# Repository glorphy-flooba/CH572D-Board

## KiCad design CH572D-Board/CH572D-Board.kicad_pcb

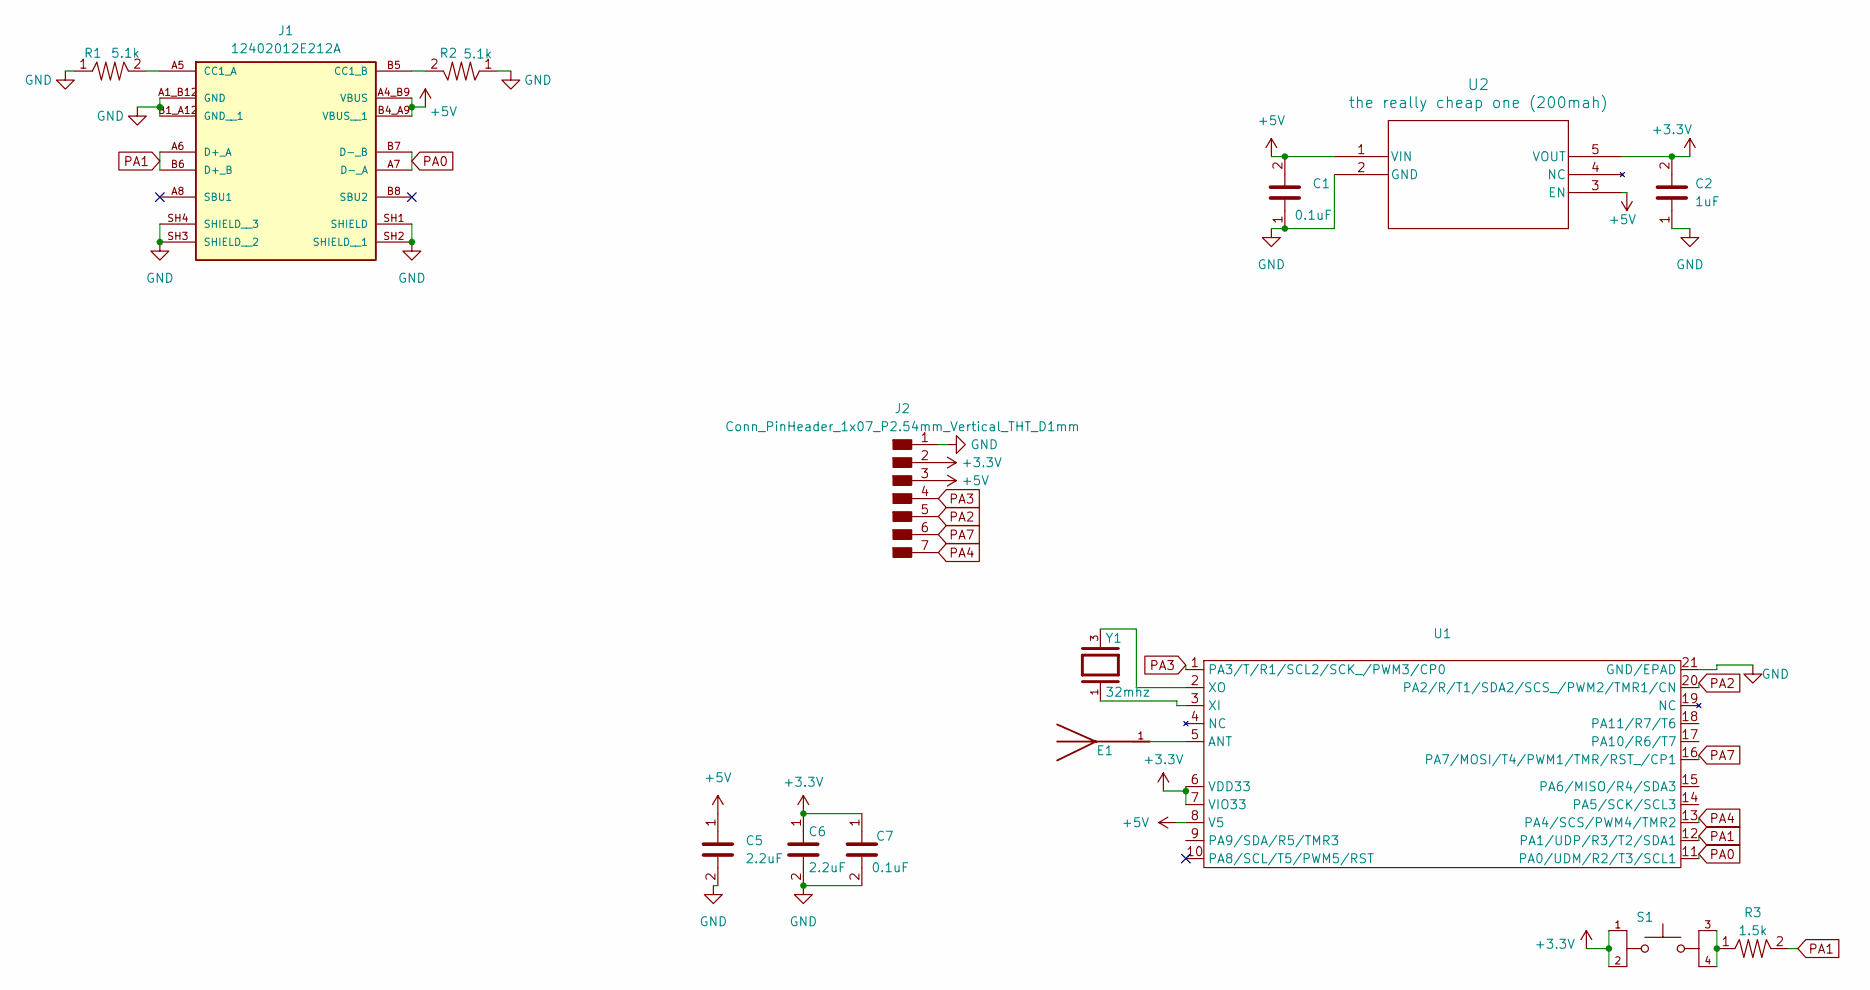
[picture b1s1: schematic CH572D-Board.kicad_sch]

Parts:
C1, C7: 0.1uF; 0603
C2: 1uF; 0603
C5, C6: 2.2uF; 0603
E1: AMCA31-2R450G-S1F-T3; DM00024648; PARTREV 03-21-19
J1: 12402012E212A; usbc; PARTREV 4
J2: Conn_PinHeader_1x07_P2.54mm_Vertical_THT_D1mm; PinHeader_01x07_P2.54mm_Vertical_THT_D1mm
R1, R2: 5.1k; 0603
R3: 1.5k; 0603
S1: TL3365AF180QG; button; PARTREV A
U1: CH572D
U2: the really cheap one (200mah); voltage regulator
Y1: 32mhz; 32mhz crystal; PARTREV N/A

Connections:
+3.3V: C2.2, C6.1, C7.1, J2.2, S1.1, S1.2, U1.6 (VDD33), U1.7 (VIO33), U2.5 (VOUT)
+5V: C1.2, C5.1, J1.A4_B9 (VBUS), J1.B4_A9 (VBUS__1), J2.3, U1.8 (V5), U2.1 (VIN), U2.3 (EN)
GND: C1.1, C2.1, C5.2, C6.2, C7.2, J1.A1_B12 (GND), J1.B1_A12 (GND__1), J1.SH1 (SHIELD), J1.SH2 (SHIELD__1), J1.SH3 (SHIELD__2), J1.SH4 (SHIELD__3), J2.1, R1.1, R2.1, U1.21 (GND/EPAD), U2.2 (GND)
unnamed: J1.A5 (CC1_A), R1.2
unnamed: J1.B5 (CC1_B), R2.2
unnamed: R3.1, S1.3, S1.4
unnamed: E1.1, U1.5 (ANT)
unnamed: U1.3 (XI), Y1.1
unnamed: U1.2 (XO), Y1.3
PA0: J1.A7 (D-_A), J1.B7 (D-_B), U1.11 (PA0/UDM/R2/T3/SCL1)
PA1: J1.A6 (D+_A), J1.B6 (D+_B), R3.2, U1.12 (PA1/UDP/R3/T2/SDA1)
PA2: J2.5, U1.20 (PA2/R/T1/SDA2/SCS_/PWM2/TMR1/CN)
PA3: J2.4, U1.1 (PA3/T/R1/SCL2/SCK_/PWM3/CP0)
PA4: J2.7, U1.13 (PA4/SCS/PWM4/TMR2)
PA7: J2.6, U1.16 (PA7/MOSI/T4/PWM1/TMR/RST_/CP1)

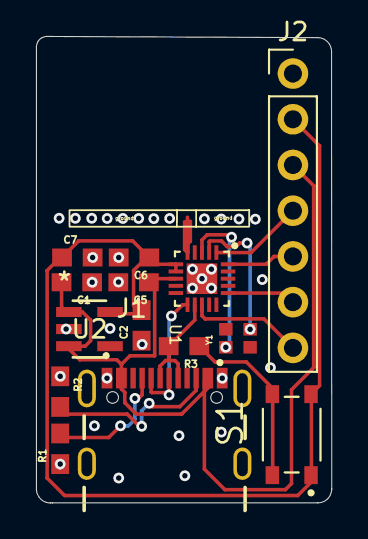
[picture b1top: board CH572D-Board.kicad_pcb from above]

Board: 2 copper layers, 16.4 x 25.9 mm, 15 parts (0 on the bottom side), 15 nets.

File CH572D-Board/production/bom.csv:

Designator,Footprint,Quantity,Value,LCSC Part #
"C1, C7",0603,2,0.1uF,
C2,0603,1,1uF,
"C5, C6",0603,2,2.2uF,
E1,DM00024648,1,AMCA31-2R450G-S1F-T3,
J1,usbc,1,12402012E212A,
J2,PinHeader_01x07_P2.54mm_Vertical_THT_D1mm,1,Conn_PinHeader_1x07_P2.54mm_Vertical_THT_D1mm,
"R1, R2",0603,2,5.1k,
R3,0603,1,1.5k,
S1,button,1,TL3365AF180QG,
U1,CH572D,1,~,
U2,voltage regulator,1,the really cheap one (200mah),
Y1,32mhz crystal,1,32mhz,

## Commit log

2025-07-06 started
2025-07-10 its basically done
2025-07-10 dont eve nknow
2025-07-16 some work
2025-07-17 nearly done
2025-07-28 big it done
    its done
2025-08-25 fixed 5v
2025-08-27 starting work on the board mk2, stripping all components off I can
2025-08-28 started slimming down
2025-09-08 small work mostlty useless
2025-09-08 fabrication output and fixed 5v
2025-09-08 redid and reordered
